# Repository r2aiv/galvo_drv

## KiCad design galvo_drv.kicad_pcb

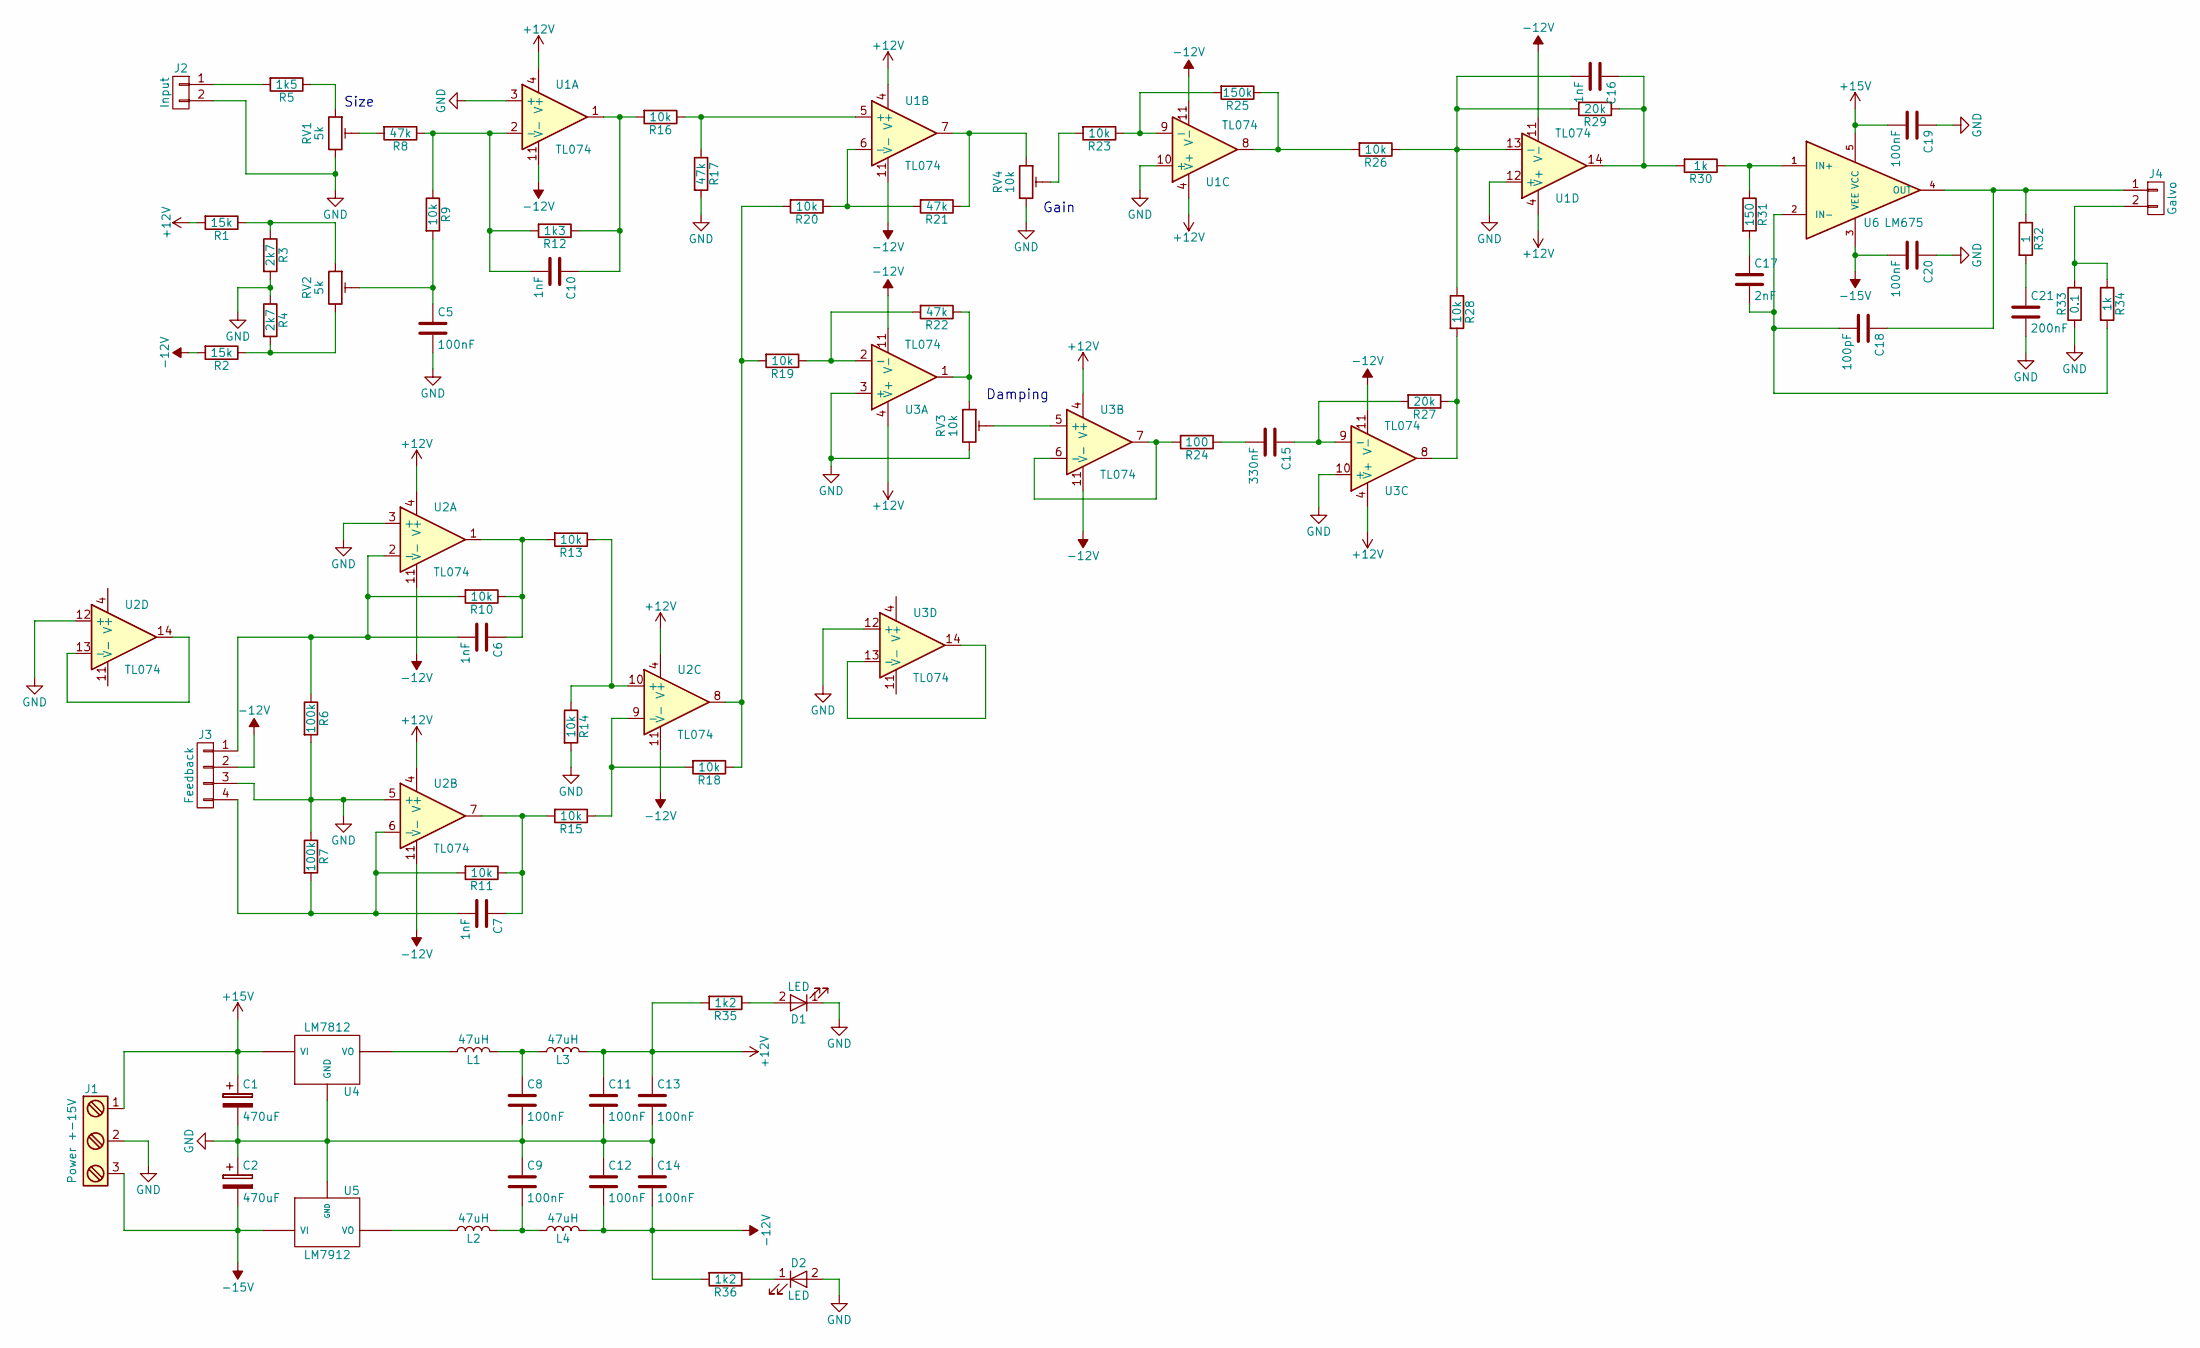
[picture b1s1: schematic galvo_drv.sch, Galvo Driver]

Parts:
C1, C2: 470uF; CP_Elec_6.3x5.7
C5, C8, C9, C11, C12, C13, C14, C19, C20: 100nF; C_0805
C6, C7, C10, C16: 1nF; C_0805
C15: 330nF; C_0805
C17: 2nF; C_0805
C18: 100pF; C_0805
C21: 200nF; C_0805
D1, D2: LED; LED_0603_HandSoldering
J1: Power +-15V; bornier3
J2: Input; Pin_Header_Straight_1x02_Pitch2.54mm
J3: Feedback; Pin_Header_Straight_1x04_Pitch2.54mm
J4: Galvo; Pin_Header_Straight_1x02_Pitch2.54mm
L1, L2, L3, L4: 47uH; L_0805
R1, R2: 15k; R_0805
R3, R4: 2k7; R_0805
R5: 1k5; R_0805
R6, R7: 100k; R_0805
R8, R17, R21, R22: 47k; R_0805
R9, R10, R11, R13, R14, R15, R16, R18, R19, R20, R23, R26, R28: 10k; R_0805
R12: 1k3; R_0805
R24: 100; R_0805
R25: 150k; R_0805
R27, R29: 20k; R_0805
R30, R34: 1k; R_0805
R31: 150; R_0805
R32: 1; R_Axial_DIN0414_L11.9mm_D4.5mm_P7.62mm_Vertical
R33: 0.1; R_Axial_DIN0414_L11.9mm_D4.5mm_P7.62mm_Vertical
R35, R36: 1k2; R_0805
RV1, RV2: 5k; Potentiometer_Trimmer_Bourns_3266W
RV3, RV4: 10k; Potentiometer_Trimmer_Bourns_3266W
U1, U2, U3: TL074; SOIC-14_3.9x8.7mm_Pitch1.27mm
U4: LM7812; TO-252-2
U5: LM7912; TO-252-2
U6: LM675; TO-263-5_TabPin3

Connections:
+12V: C11.1, C13.1, L3.2, R1.2, R35.2, U1.4 (V+), U2.4 (V+), U3.4 (V+)
+15V: C1.1, C19.2, J1.1, U4.1 (VI), U6.5 (VCC)
-12V: C12.2, C14.2, J3.2, L4.2, R2.2, R36.2, U1.11 (V-), U2.11 (V-), U3.11 (V-)
-15V: C2.2, C20.2, J1.3, U5.2 (VI), U6.3 (VEE)
unnamed: C5.1, R9.2, RV2.2
unnamed: C6.1, R10.1, R13.2, U2.1
unnamed: C6.2, J3.1, R6.1, R10.2, U2.2 (-)
unnamed: C7.1, R11.1, R15.2, U2.7
unnamed: C7.2, J3.4, R7.2, R11.2, U2.6 (-)
unnamed: C8.1, L1.2, L3.1
unnamed: C9.2, L2.2, L4.1
unnamed: C10.1, R12.1, R16.2, U1.1
unnamed: C10.2, R8.1, R9.1, R12.2, U1.2 (-)
unnamed: C15.1, R27.2, U3.9 (-)
unnamed: C15.2, R24.1
unnamed: C16.1, R29.1, R30.2, U1.14
unnamed: C16.2, R26.1, R28.1, R29.2, U1.13 (-)
unnamed: C17.1, R31.2
unnamed: C17.2, C18.2, R34.2, U6.2 (IN-)
unnamed: C18.1, J4.1, R32.1, U6.4 (OUT)
unnamed: C21.1, R32.2
unnamed: D1.2 (A), R35.1
unnamed: D2.1 (K), R36.1
unnamed: J2.1, R5.2
unnamed: J4.2, R33.2, R34.1
unnamed: L1.1, U4.3 (VO)
unnamed: L2.1, U5.3 (VO)
unnamed: R1.1, R3.1, RV2.1
unnamed: R2.1, R4.2, RV2.3
unnamed: R5.1, RV1.1
unnamed: R8.2, RV1.2
unnamed: R13.1, R14.1, U2.10 (+)
unnamed: R15.1, R18.2, U2.9 (-)
unnamed: R16.1, R17.1, U1.5 (+)
unnamed: R18.1, R19.2, R20.2, U2.8
unnamed: R19.1, R22.2, U3.2 (-)
unnamed: R20.1, R21.2, U1.6 (-)
unnamed: R21.1, RV4.1, U1.7
unnamed: R22.1, RV3.1, U3.1
unnamed: R23.1, R25.2, U1.9 (-)
unnamed: R23.2, RV4.2
unnamed: R24.2, U3.6 (-), U3.7
unnamed: R25.1, R26.2, U1.8
unnamed: R27.1, R28.2, U3.8
unnamed: R30.1, R31.1, U6.1 (IN+)
unnamed: RV3.2, U3.5 (+)

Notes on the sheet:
Damping
Gain
Size

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
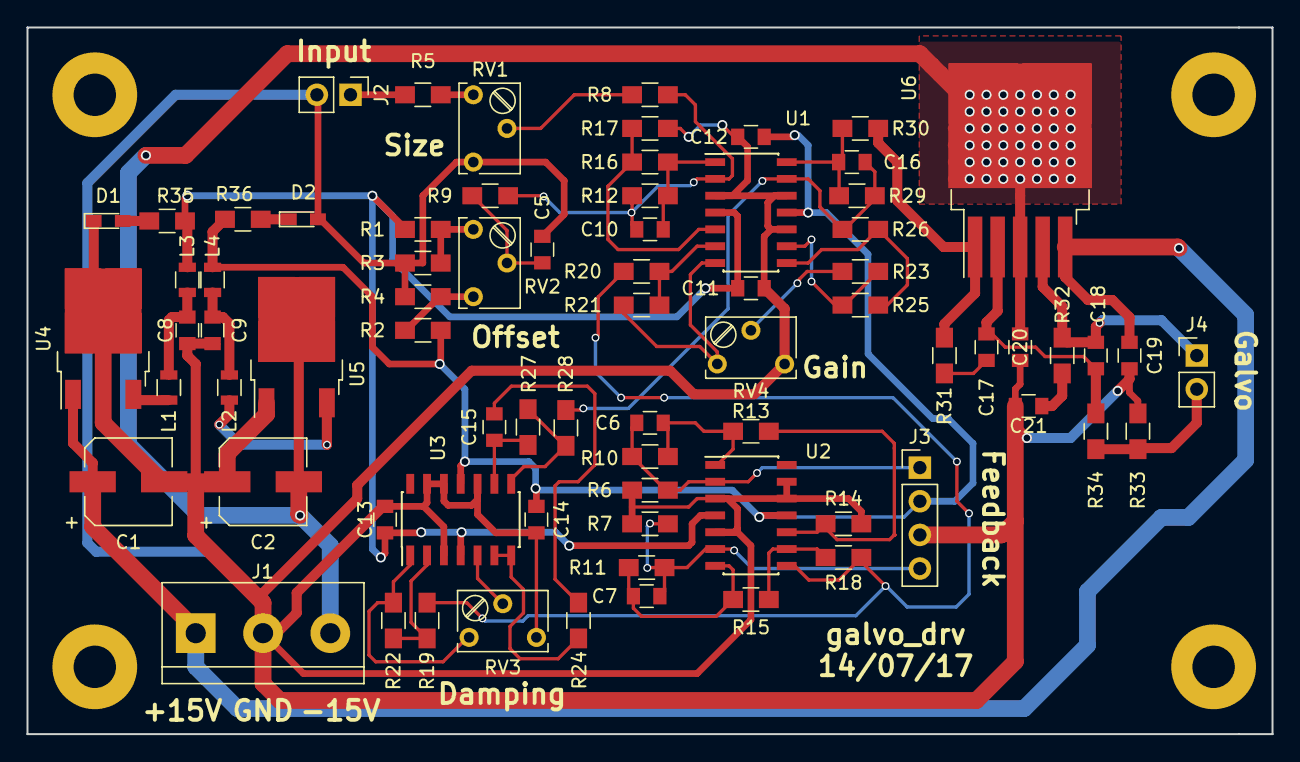
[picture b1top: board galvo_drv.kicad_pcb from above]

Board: 2 copper layers, 94.0 x 53.3 mm, 75 parts (0 on the bottom side), 47 nets.

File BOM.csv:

"R5","1k5","Resistors_SMD:R_0805",""
"RV1","5k","Potentiometers:Potentiometer_Trimmer_Bourns_3266W",""
"R8","47k","Resistors_SMD:R_0805",""
"R9","10k","Resistors_SMD:R_0805",""
"RV2","5k","Potentiometers:Potentiometer_Trimmer_Bourns_3266W",""
"R3","2k7","Resistors_SMD:R_0805",""
"R4","2k7","Resistors_SMD:R_0805",""
"R1","15k","Resistors_SMD:R_0805",""
"R2","15k","Resistors_SMD:R_0805",""
"C5","100nF","Capacitors_SMD:C_0805",""
"R12","1k3","Resistors_SMD:R_0805",""
"C10","1nF","Capacitors_SMD:C_0805",""
"R16","10k","Resistors_SMD:R_0805",""
"R17","47k","Resistors_SMD:R_0805",""
"R21","47k","Resistors_SMD:R_0805",""
"R20","10k","Resistors_SMD:R_0805",""
"R22","47k","Resistors_SMD:R_0805",""
"R19","10k","Resistors_SMD:R_0805",""
"RV3","10k","Potentiometers:Potentiometer_Trimmer_Bourns_3266W",""
"R24","100","Resistors_SMD:R_0805",""
"C15","330nF","Capacitors_SMD:C_0805",""
"R27","20k","Resistors_SMD:R_0805",""
"RV4","10k","Potentiometers:Potentiometer_Trimmer_Bourns_3266W",""
"R23","10k","Resistors_SMD:R_0805",""
"R25","150k","Resistors_SMD:R_0805",""
"R26","10k","Resistors_SMD:R_0805",""
"R28","10k","Resistors_SMD:R_0805",""
"R29","20k","Resistors_SMD:R_0805",""
"C16","1nF","Capacitors_SMD:C_0805",""
"R10","100k","Resistors_SMD:R_0805",""
"C6","1nF","Capacitors_SMD:C_0805",""
"R11","100k","Resistors_SMD:R_0805",""
"C7","1nF","Capacitors_SMD:C_0805",""
"R13","10k","Resistors_SMD:R_0805",""
"R15","10k","Resistors_SMD:R_0805",""
"R18","10k","Resistors_SMD:R_0805",""
"R14","10k","Resistors_SMD:R_0805",""
"R6","100k","Resistors_SMD:R_0805",""
"R7","100k","Resistors_SMD:R_0805",""
"J3","Feedback","Pin_Headers:Pin_Header_Straight_1x04_Pitch2.54mm",""
"U6","LM675","TO_SOT_Packages_SMD:TO-263-5_TabPin3",""
"C20","100nF","Capacitors_SMD:C_0805",""
"C19","100nF","Capacitors_SMD:C_0805",""
"R32","1","Resistors_THT:R_Axial_DIN0414_L11.9mm_D4.5mm_P7.62mm_Vertical",""
"C21","200nF","Capacitors_SMD:C_0805",""
"R33","0.1","Resistors_THT:R_Axial_DIN0414_L11.9mm_D4.5mm_P7.62mm_Vertical",""
"R34","1k","Resistors_SMD:R_0805",""
"R30","1k","Resistors_SMD:R_0805",""
"R31","150","Resistors_SMD:R_0805",""
"C17","2nF","Capacitors_SMD:C_0805",""
"C18","100pF","Capacitors_SMD:C_0805",""
"U5","LM7912","TO_SOT_Packages_SMD:TO-252-2",""
"U4","LM7812","TO_SOT_Packages_SMD:TO-252-2",""
"C1","470uF","Capacitors_SMD:CP_Elec_6.3x5.7",""
"C2","470uF","Capacitors_SMD:CP_Elec_6.3x5.7",""
"L1","L","Inductors_SMD:L_0805",""
"L2","L","Inductors_SMD:L_0805",""
"L3","L","Inductors_SMD:L_0805",""
"L4","L","Inductors_SMD:L_0805",""
"C11","100nF","Capacitors_SMD:C_0805",""
"C12","100nF","Capacitors_SMD:C_0805",""
"C13","100nF","Capacitors_SMD:C_0805",""
"C14","100nF","Capacitors_SMD:C_0805",""
"C8","100nF","Capacitors_SMD:C_0805",""
"C9","100nF","Capacitors_SMD:C_0805",""
"J1","Power +-15V","Connectors:bornier3",""
"J4","Galvo","Pin_Headers:Pin_Header_Straight_1x02_Pitch2.54mm",""
"U1","TL074","Housings_SOIC:SOIC-14_3.9x8.7mm_Pitch1.27mm",""
"U2","TL074","Housings_SOIC:SOIC-14_3.9x8.7mm_Pitch1.27mm",""
"U3","TL074","Housings_SOIC:SOIC-14_3.9x8.7mm_Pitch1.27mm",""
"R35","1k2","Resistors_SMD:R_0805",""
"D1","LED","LEDs:LED_0603_HandSoldering",""
"R36","1k2","Resistors_SMD:R_0805",""
"D2","LED","LEDs:LED_0603_HandSoldering",""
"J2","Input","Pin_Headers:Pin_Header_Straight_1x02_Pitch2.54mm",""

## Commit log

2017-08-21 Initial commit :w
